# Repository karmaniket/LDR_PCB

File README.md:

<h1 align="center">Light-Dependent-Resistor Sensor</h1>

A simple but efficient LDR sensor PCB. This PCB is made for light-sensitive applications at small scale.

## ⚡ Preview

<table>
  <tr>
    <td>
      
    </td>
    <td>
      
    </td>
  </tr>
</table>

## 🚀 Utilization

- Automatic window blinds
- Laser light security system
- Light-activated fans or doors
- Automatic street lights
- Smart lighting system
- Solar garden lights
- Energy saving system
- Smart curtains

> [!NOTE]  
> This PCB is suitable for personal projects. Significant modifications are needed for real-world or industrial applications.

## ⚙️ Requirements

- LDR
- Buzzer
- LED
- BC547 Transistor
- 200Ohm Resistor
- 9V power supply

## 📦 Installation and Setup

### Clone the repository

    git clone https://github.com/karmaniket/LDR_PCB.git
    cd LDR_PCB

### Open in KiCad

- Make desired customizations.
- In some cases you'll need to define custom footprints to match non-standard components.

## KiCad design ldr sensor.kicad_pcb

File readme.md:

<h1 align="center">LDR Sensor PCB</h1>

This repository contains the KiCad design files, Gerber outputs, and documentation for a Light Dependent Resistor (LDR) sensor PCB. The project is intended for use in light-sensing applications and is suitable for both prototyping and production.

## *Click below for full tutorial*

## Applications

- Automatic window blinds
- Laser light security system
- Light-activated fans or doors
- Automatic street lights
- Smart lighting system
- Solar garden lights
- Energy saving system
- Smart curtains

> [!NOTE]  
> This PCB is suitable for personal projects. Significant modifications are needed for real-world or industrial applications.

## Project Structure

```bash
. 
├── ldr sensor.kicad_pcb                # KiCad PCB layout file
├── ldr sensor.kicad_sch                # KiCad schematic file
├── ldr sensor.kicad_pro                # KiCad project file
├── gerber/                             # Gerber fabrication outputs
```

## Fabrication Outputs

All Gerber files required for PCB fabrication are located in the [gerber/](gerber/) directory:

```bash

**Copper Layers:**
- `ldr sensor.kicad_pc_boards-F_Cu.gbr`          # Top copper layer
- `ldr sensor.kicad_pc_boards-B_Cu.gbr`          # Bottom copper layer
**Solder Mask:**  
- `ldr sensor.kicad_pc_boards-F_Mask.gbr`        # Top solder mask, Negative polarity
- `ldr sensor.kicad_pc_boards-B_Mask.gbr`        # Bottom solder mask, Negative polarity
**Silkscreen:**  
- `ldr sensor.kicad_pc_boards-F_Silkscreen.gbr`  # Top silkscreen
- `ldr sensor.kicad_pc_boards-B_Silkscreen.gbr`  # Bottom silkscreen
**Paste Layers:**  
- `ldr sensor.kicad_pc_boards-F_Paste.gbr`       # Top paste
- `ldr sensor.kicad_pc_boards-B_Paste.gbr`       # Bottom paste
**Board Outline:**  
- `ldr sensor.kicad_pc_boards-Edge_Cuts.gbr`     # Board outline
**Job File:**  
- `ldr sensor.kicad_pc_boards-job.gbrjob`        # job file for CAM automation
```

## Setup

### 1. Clone the repository

```bash
    git clone https://github.com/karmaniket/LDR_PCB.git
    cd LDR_PCB
```

### 2. Open in KiCad

- Make desired customizations
- In some cases, you may need to define custom footprints to match non-standard components
- THT (Through-Hole Technology) components were intentionally chosen for ease of prototyping and assembly, but you can substitute SMD (Surface-Mount Device) components if preferred

### 3. Requirements

```bash
    BC547 Transistor, 200 Ohm Resistor, LDR, Buzzer, LED, 9V Battery
```

### 4. Order the PCB

- Zip all files in the [gerber/](gerber/) directory except `.gbrjob`
- Upload the ZIP to your preferred PCB manufacturer (e.g., JLCPCB, PCBWay)

Use the following specifications:

- **Layers:** 2
- **Material:** FR4
- **Thickness:** 1.6mm
- **Copper Weight:** 1oz
- **Solder Mask:** Both sides
- **Silkscreen:** Both sides
- **Surface Finish:** As required

## License

This project is licensed under the MIT License. Feel free to use, modify and distribute with attribution.

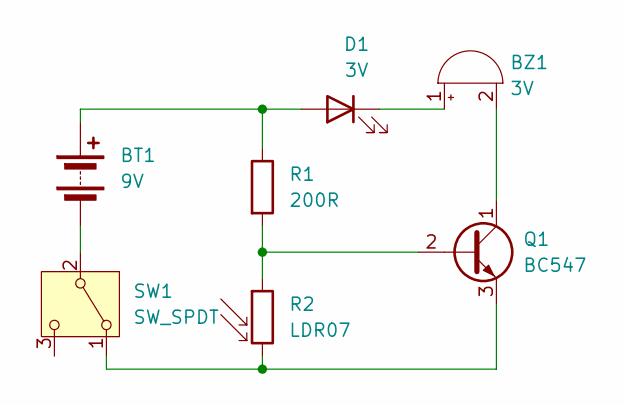
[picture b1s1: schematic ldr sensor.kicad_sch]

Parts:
BT1: 9V; Battery
BZ1: 3V; Buzzer_15x7.5RM7.6
D1: 3V; LED_D5.0mm_Clear
Q1: BC547; TO-92_Inline
R1: 200R; R_Axial_DIN0207_L6.3mm_D2.5mm_P10.16mm_Horizontal
R2: LDR07; R_LDR_5.1x4.3mm_P3.4mm_Vertical
SW1: SW_SPDT; SW_CK_JS202011CQN_DPDT_Straight

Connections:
unnamed: BT1.1 (+), D1.2 (A), R1.1
unnamed: BT1.2 (-), SW1.2 (B)
unnamed: BZ1.1 (+), D1.1 (K)
unnamed: BZ1.2 (-), Q1.1 (C)
unnamed: Q1.2 (B), R1.2, R2.1
unnamed: Q1.3 (E), R2.2, SW1.1 (A)

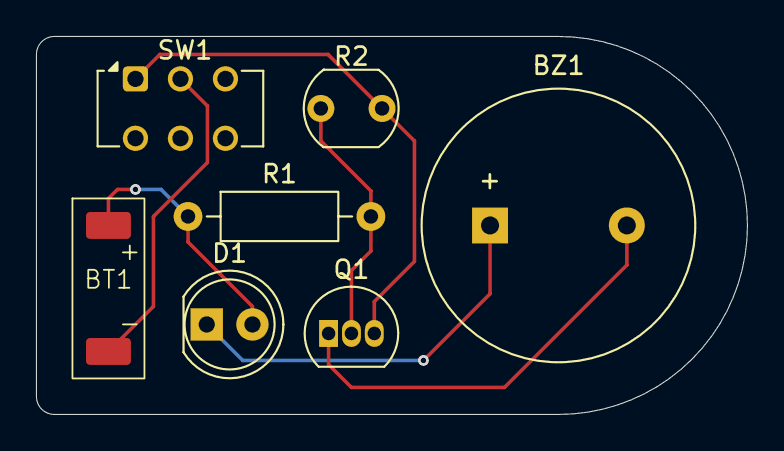
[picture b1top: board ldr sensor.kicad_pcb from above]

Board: 2 copper layers, 39.5 x 21.0 mm, 7 parts (0 on the bottom side), 6 nets.

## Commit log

2025-04-21 Create LICENSE
